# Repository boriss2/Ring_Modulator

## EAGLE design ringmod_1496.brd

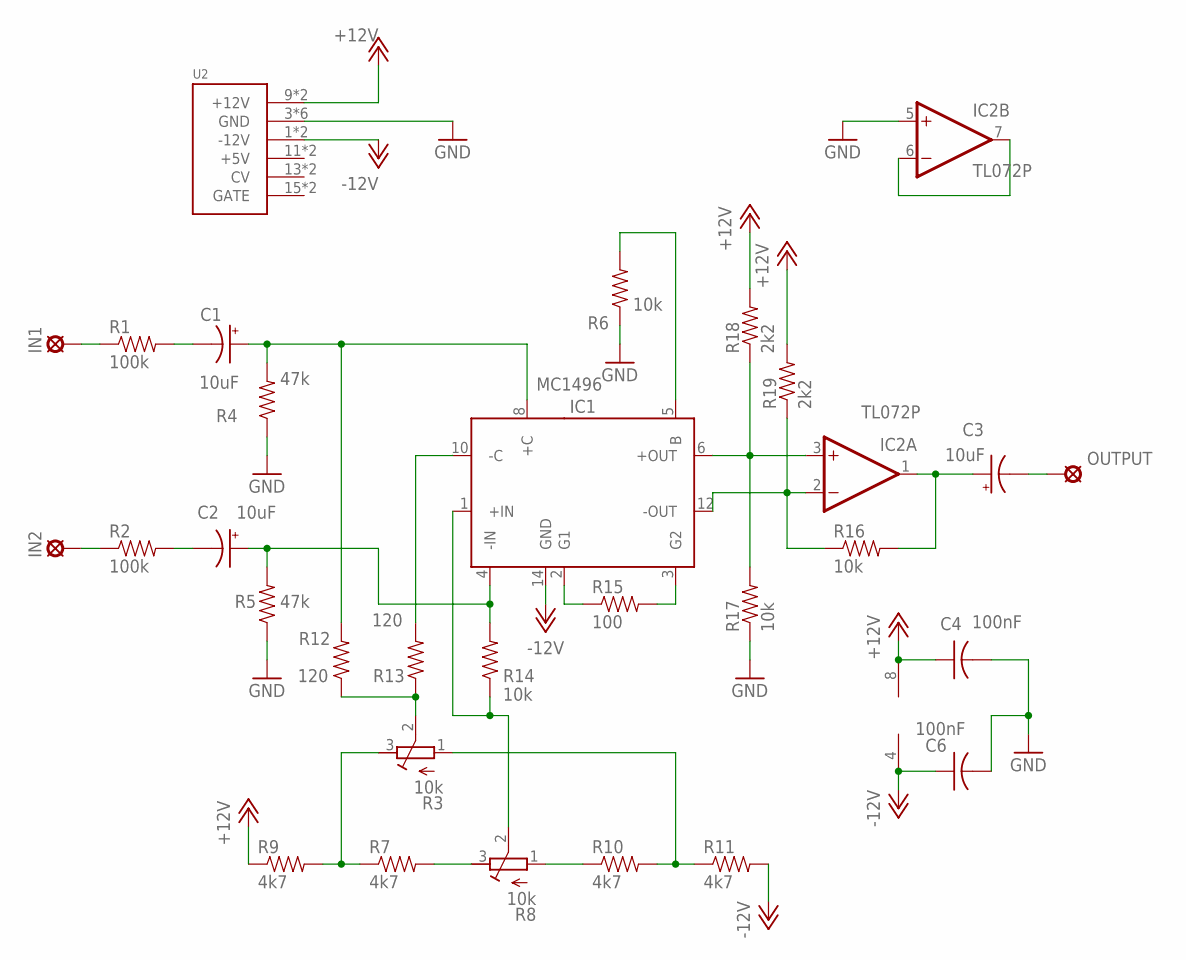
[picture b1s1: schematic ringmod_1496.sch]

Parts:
C1, C2, C3: 10uF; B45181A
C4, C6: 100nF; C025-024X044
IC1: MC1496
IC2: TL072P; DIL08
IN1, IN2: LSP11
OUTPUT: LSP11
R1, R2: 100k; AXIAL-0.4
R3, R8: 10k; RTRIM64W
R4, R5: 47k; AXIAL-0.4
R6, R14, R16, R17: 10k; AXIAL-0.4
R7, R9, R10, R11: 4k7; AXIAL-0.4
R12, R13: 120; AXIAL-0.4
R15: 100; AXIAL-0.4
R18, R19: 2k2; AXIAL-0.4
U2: POWER; POWER_16

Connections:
+12V: C4.1, IC2.8 (V+), R9.P$1 (1), R18.P$2 (2), R19.P$2 (2), U2.9 (+12V), U2.10 (+12V)
-12V: C6.1, IC1.14 (GND), IC2.4 (V-), R11.P$2 (2), U2.1 (-12V), U2.2 (-12V)
GND: C4.2, C6.2, IC2.5 (+IN), R4.P$1 (1), R5.P$1 (1), R6.P$1 (1), R17.P$1 (1), U2.3 (GND), U2.4 (GND), U2.5 (GND), U2.6 (GND), U2.7 (GND), U2.8 (GND)
unnamed: IN1.MP, R1.P$1 (1)
unnamed: IN2.MP, R2.P$1 (1)
unnamed: C1.-, R1.P$2 (2)
unnamed: C2.-, R2.P$2 (2)
unnamed: R3.3 (E), R7.P$1 (1), R9.P$2 (2)
unnamed: IC1.5 (B), R6.P$2 (2)
unnamed: C1.+, IC1.8 (+C), R4.P$2 (2), R12.P$2 (2)
unnamed: C2.+, IC1.4 (-IN), R5.P$2 (2), R14.P$2 (2)
unnamed: R7.P$2 (2), R8.3 (E)
unnamed: R8.1 (A), R10.P$1 (1)
unnamed: R3.1 (A), R10.P$2 (2), R11.P$1 (1)
unnamed: R3.2 (S), R12.P$1 (1), R13.P$1 (1)
unnamed: IC1.10 (-C), R13.P$2 (2)
unnamed: IC1.1 (+IN), R8.2 (S), R14.P$1 (1)
unnamed: IC1.2 (G1), R15.P$1 (1)
unnamed: IC1.3 (G2), R15.P$2 (2)
unnamed: C3.-, OUTPUT.MP
unnamed: C3.+, IC2.1 (OUT), R16.P$2 (2)
unnamed: IC1.12 (-OUT), IC2.2 (-IN), R16.P$1 (1), R19.P$1 (1)
unnamed: IC1.6 (+OUT), IC2.3 (+IN), R17.P$2 (2), R18.P$1 (1)
unnamed: IC2.6 (-IN), IC2.7 (OUT)

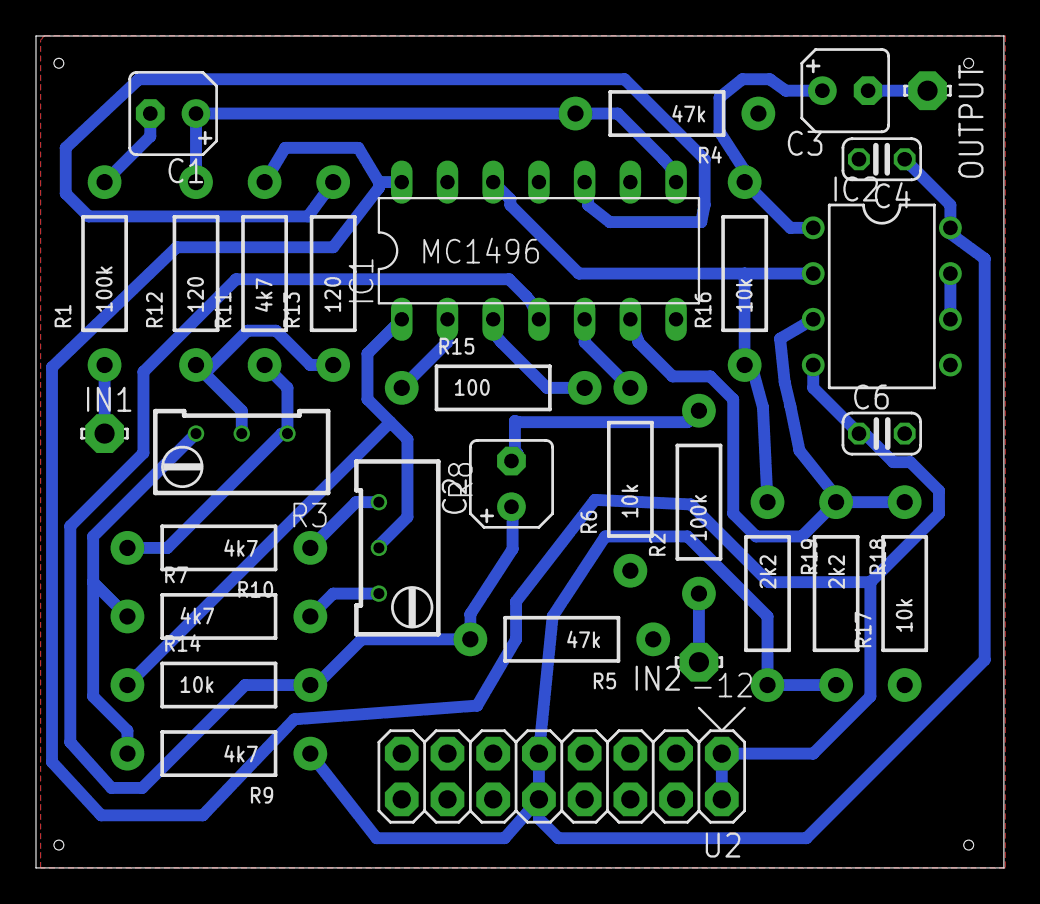
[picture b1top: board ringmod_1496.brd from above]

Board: 2 copper layers, 53.8 x 46.2 mm, 30 parts (0 on the bottom side), 24 nets.

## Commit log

2022-04-26 initial check in
2022-04-27 Code Cleanup
2022-05-05 Added Antenna Amp

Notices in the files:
parts and their libraries:
SparkFun-Resistors: Licensing: Creative Commons ShareAlike 4.0 International - https://creativecommons.org/licenses/by-sa/4.0
